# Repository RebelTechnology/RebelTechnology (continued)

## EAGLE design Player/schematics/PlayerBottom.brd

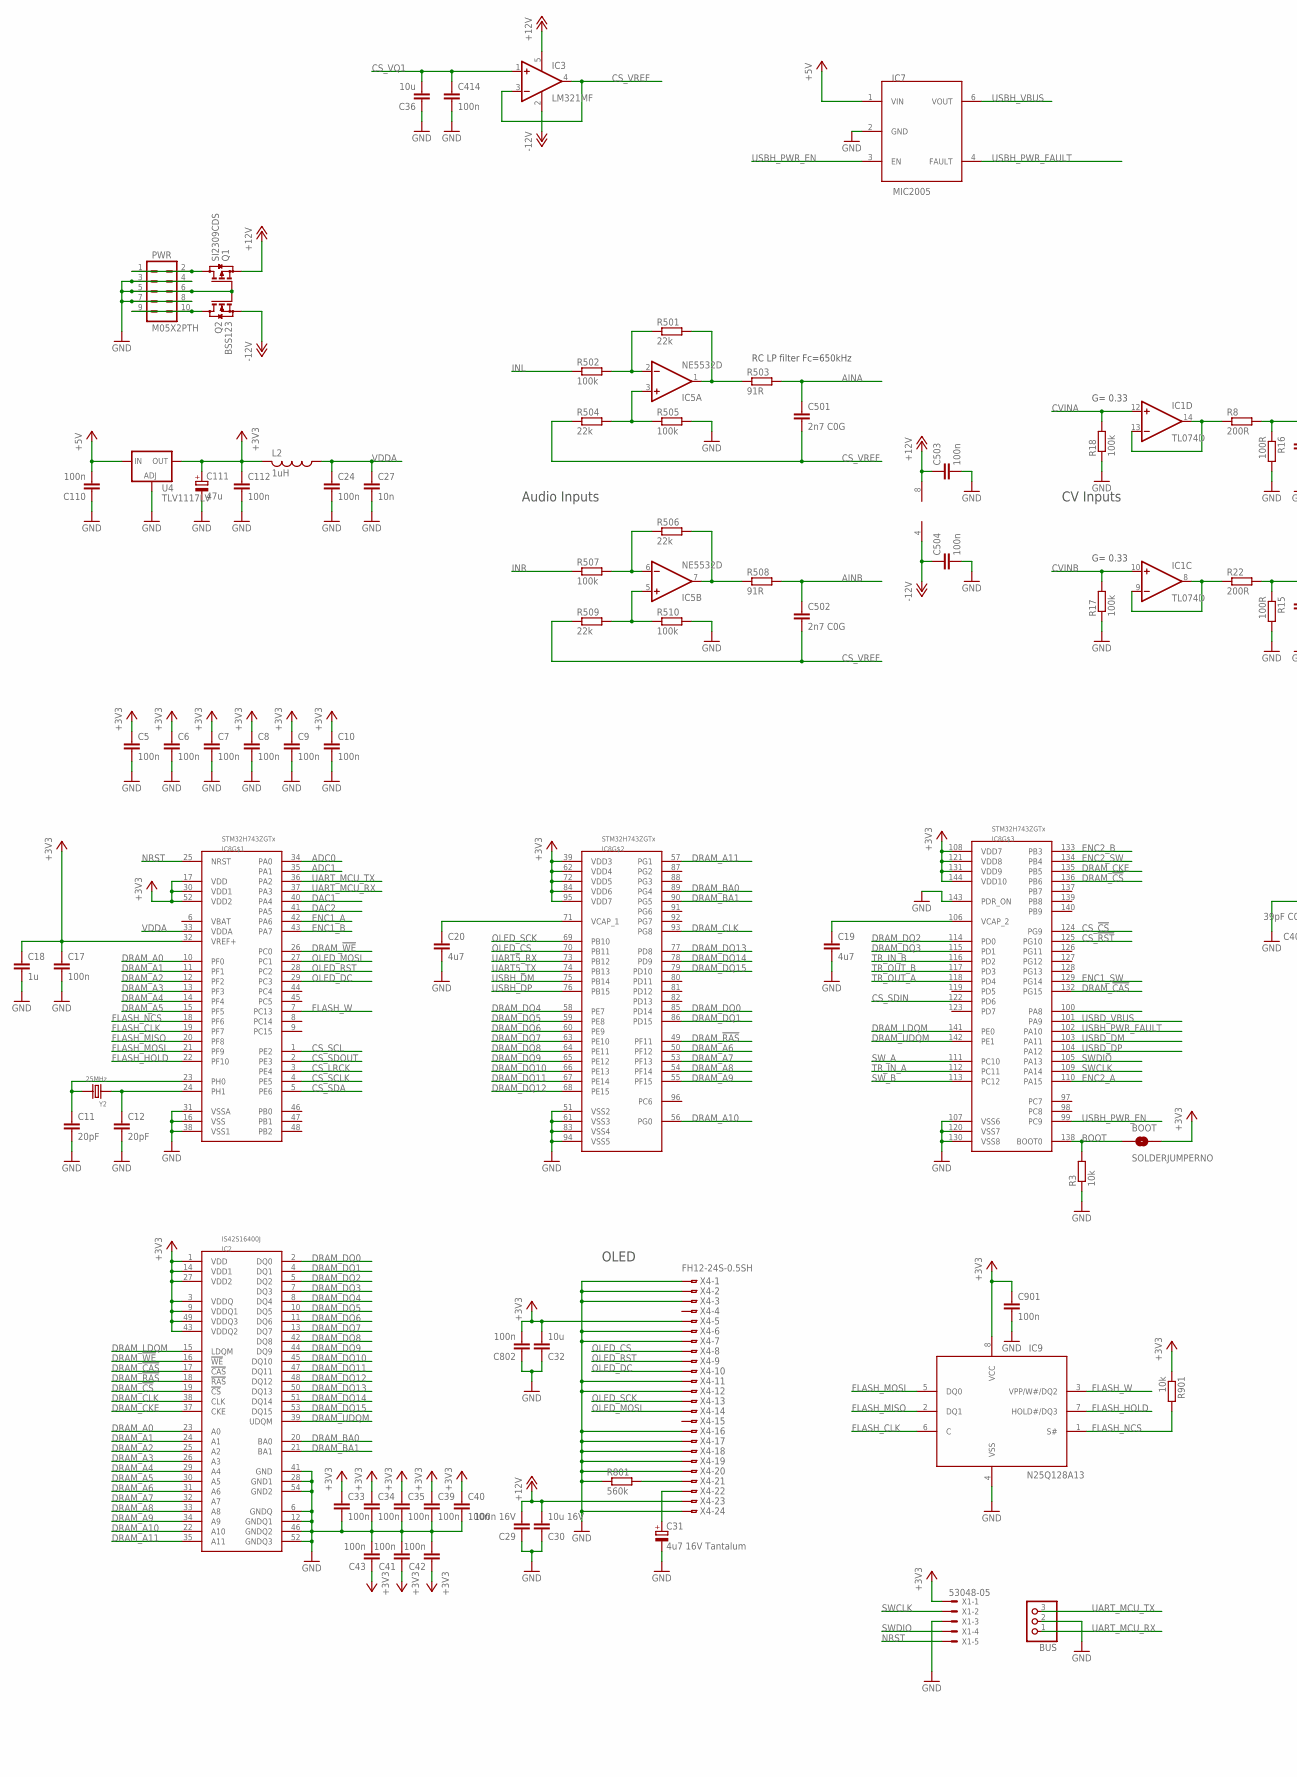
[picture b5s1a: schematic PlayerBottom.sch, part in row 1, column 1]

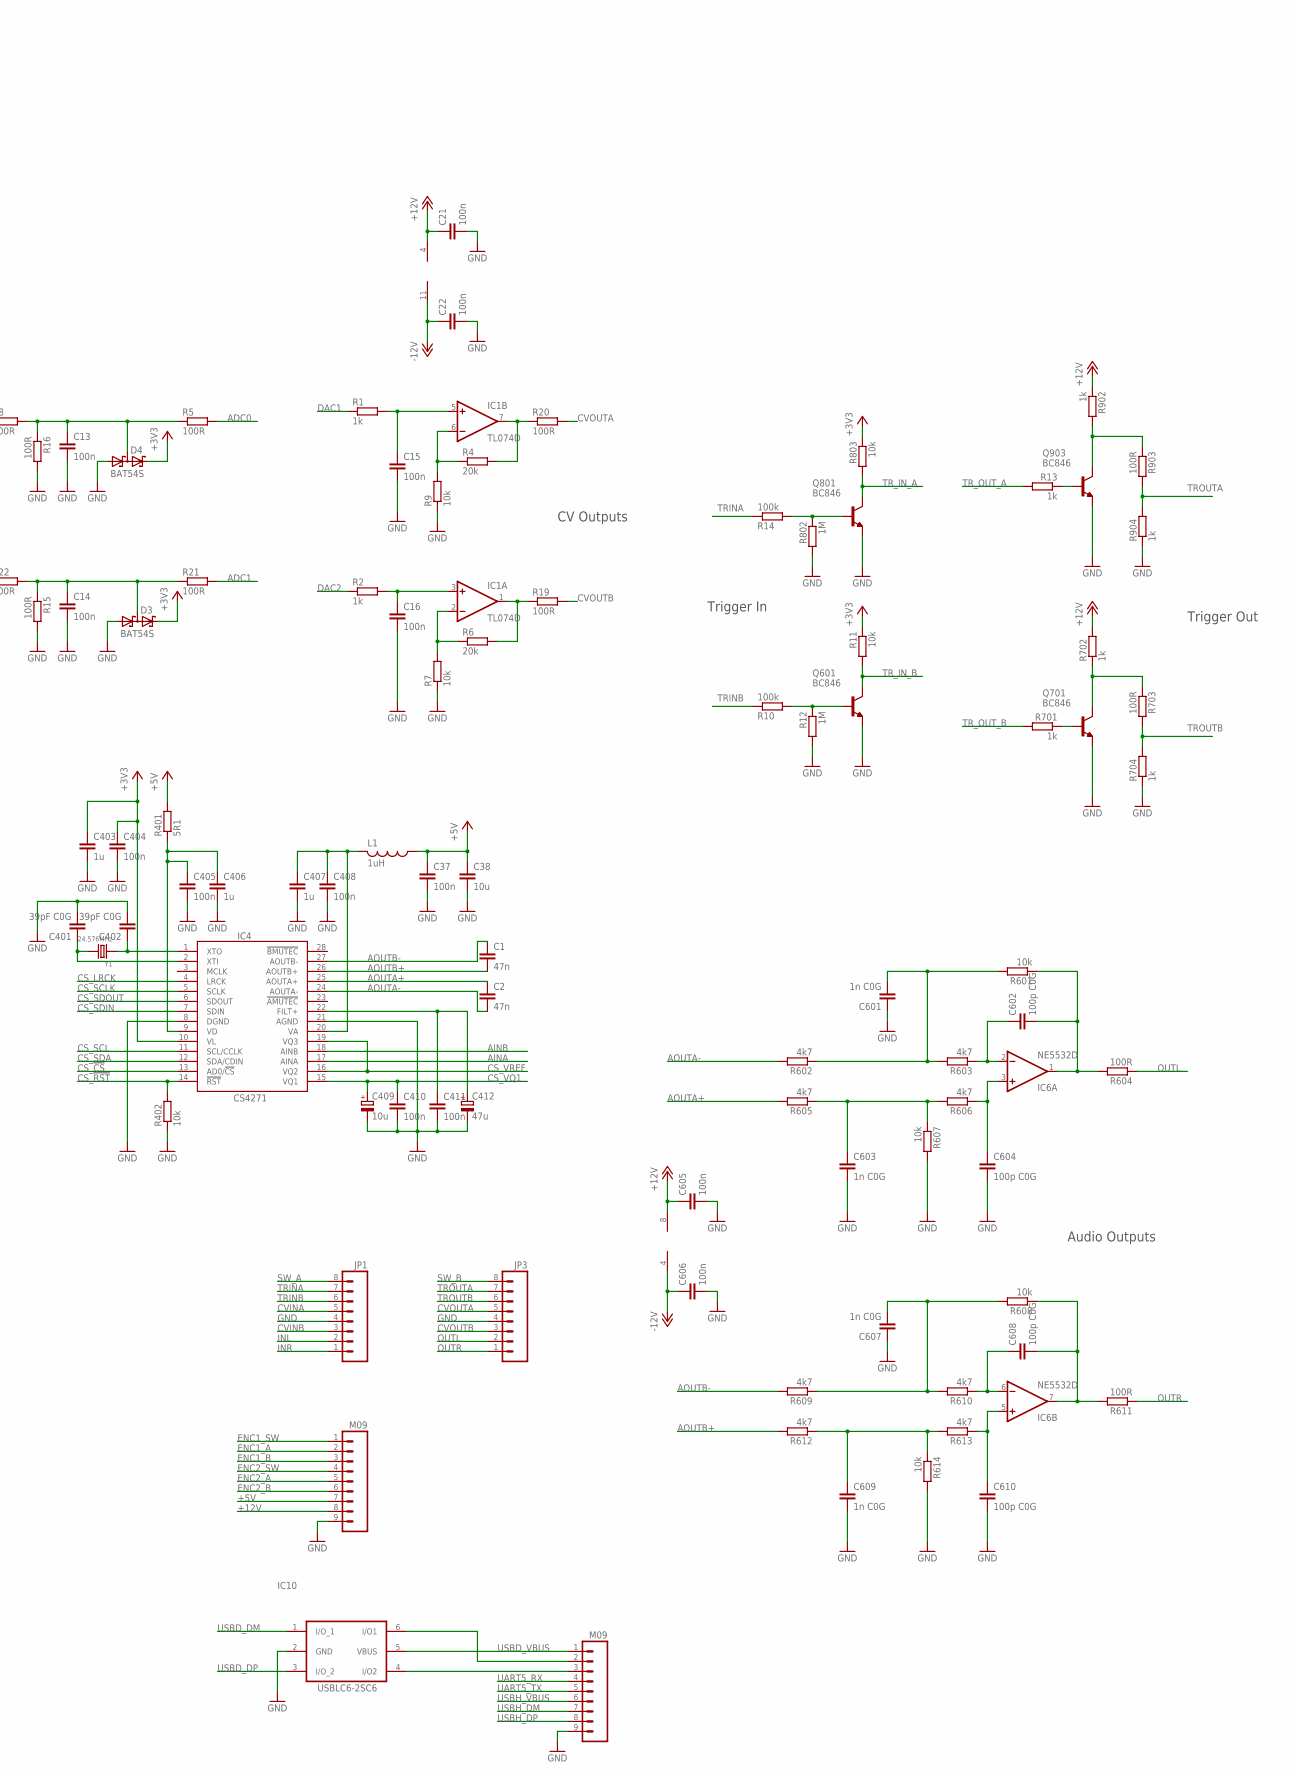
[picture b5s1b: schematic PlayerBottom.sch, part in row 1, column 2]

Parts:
BOOT: SOLDERJUMPERNO; SJ_2S-NO
BUS: CON-JST-1X03PH-TH; JST-B3B-PH-KL
C1, C2: 47n; C0603
C5, C6, C7, C8, C9, C10, C13, C14, C15, C16, C17, C21, C22, C24, C33, C34, C35, C37, C39, C40, C41, C42, C43, C110, C112, C404, C405, C408, C410, C411, C414, C503, C504, C605, C606, C802, C901: 100n; C0603
C11, C12: 20pF; C0603
C18, C403, C406, C407: 1u; C0603
C19, C20: 4u7; C0603
C27: 10n; C0603
C29: 100n 16V; C0603
C30: 10u 16V; C1206
C31: 4u7 16V Tantalum; SMC_A
C32, C36, C38: 10u; C1206
C111, C412: 47u; CPOL-5
C401, C402: 39pF C0G; C0603
C409: 10u; CPOL-5
C501, C502: 2n7 C0G; C0603
C601, C603, C607, C609: 1n C0G; C0603
C602, C604, C608, C610: 100p C0G; C0603
D3, D4: BAT54S; SOT23
IC1: TL074D; SO14
IC2: IS42S16400J; TSOP54-400
IC3: LM321MF; SOT23-5
IC4: CS4271; TSSOP28-0.65-9.7X4.4MM
IC5, IC6: NE5532D; SO08
IC7: MIC2005; SOT23-6
IC8: STM32H743ZGTx; QFP50P2200X2200X160-144N
IC9: N25Q128A13; SO8W
IC10: USBLC6-2SC6; SOT-23-6L
JP1, JP3: M081X08; 1X08
JP2, JP4: M09; 1X09
L1, L2: 1uH; 0603
PWR: M05X2PTH; AVR_ICSP
Q1: SI2309CDS; SOT23
Q2: BSS123; SOT23
Q601, Q701, Q801, Q903: BC846; SOT23
R1, R2, R13, R701, R702, R704, R902, R904: 1k; 0603
R3, R7, R9, R11, R402, R601, R607, R608, R614, R803, R901: 10k; 0603
R4, R6: 20k; 0603
R5, R15, R16, R19, R20, R21, R604, R611, R703, R903: 100R; 0603
R8, R22: 200R; 0603
R10, R14, R17, R18, R502, R505, R507, R510: 100k; 0603
R12, R802: 1M; 0603
R401: 5R1; 0603
R501, R504, R506, R509: 22k; 0603
R503, R508: 91R; 0603
R602, R603, R605, R606, R609, R610, R612, R613: 4k7; 0603
R801: 560k; 0603
U4: TLV1117LV; SOT223
X1: 53048-05
X4: FH12-24S-0.5SH
Y1: 24.576MHz; X2-SMD-5.0X3.2X1.3MM
Y2: 25MHz; X2-SMD-5.0X3.2X1.3MM

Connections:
+3.3V: BOOT.2, C5.1, C6.1, C7.1, C8.1, C9.1, C10.1, C17.1, C18.1, C32.2, C33.1, C34.1, C35.1, C39.1, C40.1, C41.1, C42.1, C43.1, C111.+, C112.1, C403.1, C404.1, C802.2, C901.1, D3.2 (C2), D4.2 (C2), IC2.1 (VDD), IC2.3 (VDDQ), IC2.9 (VDDQ1), IC2.14 (VDD1), IC2.27 (VDD2), IC2.43 (VDDQ2), IC2.49 (VDDQ3), IC4.10 (VL), IC8.17 (VDD), IC8.30 (VDD1), IC8.32 (VREF+), IC8.39 (VDD3), IC8.52 (VDD2), IC8.62 (VDD4), IC8.72 (VDD5), IC8.84 (VDD6), IC8.95 (VDD7), IC8.108 (VDD7), IC8.121 (VDD8), IC8.131 (VDD9), IC8.144 (VDD10), IC9.8 (VCC), L2.2, R11.1, R803.1, R901.1, U4.4 (OUT), X1.1, X4.5
+5V: C37.1, C38.1, C110.2, IC7.1 (VIN), JP4.7, L1.1, R401.2, U4.3 (IN)
+12V: C21.1, C29.2, C30.2, C503.1, C605.1, IC1.4 (V+), IC3.5 (V+), IC5.8 (V+), IC6.8 (V+), JP4.8, Q1.2 (S), R702.2, R902.1, X4.23
-12V: C22.1, C504.1, C606.1, IC1.11 (V-), IC3.2 (V-), IC5.4 (V-), IC6.4 (V-), Q2.2 (S)
ADC0: IC8.34 (PA0), R5.2
ADC1: IC8.35 (PA1), R21.2
AINA: C501.1, IC4.17 (AINA), R503.2
AINB: C502.1, IC4.18 (AINB), R508.2
ANALOG_OUTA: C602.2, IC6.1 (OUT), R601.1, R604.2
ANALOG_OUTB: C608.2, IC6.7 (OUT), R608.1, R611.2
AOUTA+: C2.1, IC4.25 (AOUTA+), R605.2
AOUTA-: C2.2, IC4.24 (AOUTA-), R602.2
AOUTB+: C1.2, IC4.26 (AOUTB+), R612.2
AOUTB-: C1.1, IC4.27 (AOUTB-), R609.2
BOOT: BOOT.1, IC8.138 (BOOT0), R3.2
CS_!CS: IC4.13 (AD0/!CS), IC8.124 (PG9)
CS_!RST: IC4.14 (!RST), IC8.125 (PG10), R402.2
CS_LRCK: IC4.4 (LRCK), IC8.3 (PE4)
CS_SCK: IC4.11 (SCL/CCLK), IC8.1 (PE2)
CS_SCLK: IC4.5 (SCLK), IC8.4 (PE5)
CS_SDA: IC4.12 (SDA/CDIN), IC8.5 (PE6)
CS_SDIN: IC4.7 (SDIN), IC8.122 (PD6)
CS_SDOUT: IC4.6 (SDOUT), IC8.2 (PE3)
CS_VQ1: C36.2, C409.+, C410.1, C414.1, IC3.1 (+IN), IC4.15 (VQ1)
CS_VREF: C501.2, C502.2, IC3.3 (-IN), IC3.4 (OUT), IC4.16 (VQ2), IC4.19 (VQ3), R504.1, R509.1
CVINA: IC1.12 (+IN), JP1.5, R18.2
CVINB: IC1.10 (+IN), JP1.3, R17.2
CVOUTA: JP3.5, R20.2
CVOUTB: JP3.3, R19.2
DAC1: IC8.40 (PA4), R1.1
DAC2: IC8.41 (PA5), R2.1
DRAM_!CAS: IC2.17 (!CAS), IC8.132 (PG15)
DRAM_!CS: IC2.19 (!CS), IC8.136 (PB6)
DRAM_!RAS: IC2.18 (!RAS), IC8.49 (PF11)
DRAM_!WE: IC2.16 (!WE), IC8.26 (PC0)
DRAM_A0: IC2.23 (A0), IC8.10 (PF0)
DRAM_A1: IC2.24 (A1), IC8.11 (PF1)
DRAM_A2: IC2.25 (A2), IC8.12 (PF2)
DRAM_A3: IC2.26 (A3), IC8.13 (PF3)
DRAM_A4: IC2.29 (A4), IC8.14 (PF4)
DRAM_A5: IC2.30 (A5), IC8.15 (PF5)
DRAM_A6: IC2.31 (A6), IC8.50 (PF12)
DRAM_A7: IC2.32 (A7), IC8.53 (PF13)
DRAM_A8: IC2.33 (A8), IC8.54 (PF14)
DRAM_A9: IC2.34 (A9), IC8.55 (PF15)
DRAM_A10: IC2.22 (A10), IC8.56 (PG0)
DRAM_A11: IC2.35 (A11), IC8.57 (PG1)
DRAM_BA0: IC2.20 (BA0), IC8.89 (PG4)
DRAM_BA1: IC2.21 (BA1), IC8.90 (PG5)
DRAM_CKE: IC2.37 (CKE), IC8.135 (PB5)
DRAM_CLK: IC2.38 (CLK), IC8.93 (PG8)
DRAM_DQ0: IC2.2 (DQ0), IC8.85 (PD14)
DRAM_DQ1: IC2.4 (DQ1), IC8.86 (PD15)
DRAM_DQ2: IC2.5 (DQ2), IC8.114 (PD0)
DRAM_DQ3: IC2.7 (DQ3), IC8.115 (PD1)
DRAM_DQ4: IC2.8 (DQ4), IC8.58 (PE7)
DRAM_DQ5: IC2.10 (DQ5), IC8.59 (PE8)
DRAM_DQ6: IC2.11 (DQ6), IC8.60 (PE9)
DRAM_DQ7: IC2.13 (DQ7), IC8.63 (PE10)
DRAM_DQ8: IC2.42 (DQ8), IC8.64 (PE11)
DRAM_DQ9: IC2.44 (DQ9), IC8.65 (PE12)
DRAM_DQ10: IC2.45 (DQ10), IC8.66 (PE13)
DRAM_DQ11: IC2.47 (DQ11), IC8.67 (PE14)
DRAM_DQ12: IC2.48 (DQ12), IC8.68 (PE15)
DRAM_DQ13: IC2.50 (DQ13), IC8.77 (PD8)
DRAM_DQ14: IC2.51 (DQ14), IC8.78 (PD9)
DRAM_DQ15: IC2.53 (DQ15), IC8.79 (PD10)
DRAM_LDQM: IC2.15 (LDQM), IC8.141 (PE0)
DRAM_UDQM: IC2.39 (UDQM), IC8.142 (PE1)
ENC1_A: IC8.42 (PA6), JP4.2
ENC1_B: IC8.43 (PA7), JP4.3
ENC1_SW: IC8.129 (PG14), JP4.1
ENC2_A: IC8.110 (PA15), JP4.5
ENC2_B: IC8.133 (PB3), JP4.6
ENC2_SW: IC8.134 (PB4), JP4.4
FLASH_CLK: IC8.19 (PF7), IC9.6 (C)
FLASH_HOLD: IC8.22 (PF10), IC9.7 (HOLD#/DQ3)
FLASH_MISO: IC8.20 (PF8), IC9.2 (DQ1)
FLASH_MOSI: IC8.21 (PF9), IC9.5 (DQ0)
FLASH_NCS: IC8.18 (PF6), IC9.1 (S#), R901.2
FLASH_W: IC8.7 (PC13), IC9.3 (VPP/W#/DQ2)
GND: BUS.2, C5.2, C6.2, C7.2, C8.2, C9.2, C10.2, C11.2, C12.2, C13.2, C14.2, C15.2, C16.2, C17.2, C18.2, C19.2, C20.2, C21.2, C22.2, C24.2, C27.2, C29.1, C30.1, C31.-, C31.C, C32.1, C33.2, C34.2, C35.2, C36.1, C37.2, C38.2, C39.2, C40.2, C41.2, C42.2, C43.2, C110.1, C111.-, C112.2, C401.2, C402.2, C403.2, C404.2, C405.2, C406.2, C407.2, C408.2, C409.-, C410.2, C411.2, C412.-, C414.2, C503.2, C504.2, C601.1, C603.2, C604.2, C605.2, C606.2, C607.1, C609.2, C610.2, C802.1, C901.2, D3.1 (A1), D4.1 (A1), IC2.6 (GNDQ), IC2.12 (GNDQ1), IC2.28 (GND1), IC2.41 (GND), IC2.46 (GNDQ2), IC2.52 (GNDQ3), IC2.54 (GND2), IC4.8 (DGND), IC4.21 (AGND), IC7.2 (GND), IC8.16 (VSS), IC8.31 (VSSA), IC8.38 (VSS1), IC8.51 (VSS2), IC8.61 (VSS3), IC8.83 (VSS4), IC8.94 (VSS5), IC8.107 (VSS6), IC8.120 (VSS7), IC8.130 (VSS8), IC8.143 (PDR_ON), IC9.4 (VSS), IC10.2 (GND), JP1.4, JP2.9, JP3.4, JP4.9, PWR.3, PWR.4, PWR.5, PWR.6, PWR.7, PWR.8, Q1.1 (G), Q2.1 (G), Q601.2 (E), Q701.2 (E), Q801.2 (E), Q903.2 (E), R3.1, R7.1, R9.1, R12.2, R15.2, R16.2, R17.1, R18.1, R402.1, R505.2, R510.2, R607.2, R614.2, R704.1, R801.1, R802.2, R904.1, U4.1 (ADJ), X1.3, X4.1, X4.2, X4.3, X4.6, X4.7, X4.11, X4.12, X4.16, X4.17, X4.18, X4.19, X4.20, X4.24
INL: JP1.2, R502.1
INR: JP1.1, R507.1
unnamed: C603.1, R605.1, R606.2, R607.1
unnamed: C13.1, D4.3 (C1A2), R5.1, R8.2, R16.1
unnamed: C407.1, C408.1, IC4.20 (VA), L1.2
unnamed: IC1.7 (OUT), R4.2, R20.1
unnamed: IC1.8 (OUT), IC1.9 (-IN), R22.1
unnamed: C31.+, C31.A, X4.22
unnamed: PWR.9, PWR.10, Q2.3 (D)
unnamed: R801.2, X4.21
unnamed: PWR.1, PWR.2, Q1.3 (D)
unnamed: C601.2, R601.2, R602.1, R603.2
unnamed: C12.1, IC8.24 (PH1), Y2.1
unnamed: IC1.2 (-IN), R6.1, R7.2
unnamed: C602.1, IC6.2 (-IN), R603.1
unnamed: C604.1, IC6.3 (+IN), R606.1
unnamed: IC1.6 (-IN), R4.1, R9.2
unnamed: C11.1, IC8.23 (PH0), Y2.2
unnamed: C402.1, IC4.1 (XTO), Y1.1
unnamed: IC10.6 (I/O1), JP2.2
unnamed: C411.1, C412.+, IC4.22 (FILT+)
unnamed: C401.1, IC4.2 (XTI), Y1.2
unnamed: C14.1, D3.3 (C1A2), R15.1, R21.1, R22.2
unnamed: C609.1, R612.1, R613.2, R614.1
unnamed: C607.2, R608.2, R609.1, R610.2
unnamed: C608.1, IC6.6 (-IN), R610.1
unnamed: C610.1, IC6.5 (+IN), R613.1
unnamed: IC1.13 (-IN), IC1.14 (OUT), R8.1
unnamed: C16.1, IC1.3 (+IN), R2.2
unnamed: IC1.1 (OUT), R6.2, R19.1
unnamed: C19.1, IC8.106 (VCAP_2)
unnamed: C20.1, IC8.71 (VCAP_1)
unnamed: IC5.3 (+IN), R504.2, R505.1
unnamed: Q601.1 (B), R10.2, R12.1
unnamed: IC5.2 (-IN), R501.1, R502.2
unnamed: Q701.1 (B), R701.1
unnamed: IC5.1 (OUT), R501.2, R503.1
unnamed: Q701.3 (C), R702.1, R703.1
unnamed: IC5.5 (+IN), R509.2, R510.1
unnamed: IC5.6 (-IN), R506.1, R507.2
unnamed: C15.1, IC1.5 (+IN), R1.2
unnamed: IC5.7 (OUT), R506.2, R508.1
unnamed: Q903.1 (B), R13.1
unnamed: Q903.3 (C), R902.2, R903.1
unnamed: Q801.1 (B), R14.2, R802.1
unnamed: IC10.4 (I/O2), JP2.3
NRST: IC8.25 (NRST), X1.5
OLED_CS: IC8.70 (PB11), X4.8
OLED_DC: IC8.29 (PC3), X4.10
OLED_MOSI: IC8.27 (PC1), X4.14
OLED_RST: IC8.28 (PC2), X4.9
OLED_SCK: IC8.69 (PB10), X4.13
OUTL: JP3.2, R604.1
OUTR: JP3.1, R611.1
SWCLK: IC8.109 (PA14), X1.2
SWDIO: IC8.105 (PA13), X1.4
SW_A: IC8.111 (PC10), JP1.8
SW_B: IC8.113 (PC12), JP3.8
TRINA: JP1.7, R14.1
TRINB: JP1.6, R10.1
TROUTA: JP3.7, R903.2, R904.2
TROUTB: JP3.6, R703.2, R704.2
TR_IN_A: IC8.112 (PC11), Q801.3 (C), R803.2
TR_IN_B: IC8.116 (PD2), Q601.3 (C), R11.2
TR_OUT_A: IC8.118 (PD4), R13.2
TR_OUT_B: IC8.117 (PD3), R701.2
UART5_RX: IC8.73 (PB12), JP2.4
UART5_TX: IC8.74 (PB13), JP2.5
UART_MCU_RX: BUS.1, IC8.37 (PA3)
UART_MCU_TX: BUS.3, IC8.36 (PA2)
USBD_DM: IC8.103 (PA11), IC10.1 (I/O_1)
USBD_DP: IC8.104 (PA12), IC10.3 (I/O_2)
USBD_VBUS: IC8.101 (PA9), IC10.5 (VBUS), JP2.1
USBH_DM: IC8.75 (PB14), JP2.7
USBH_DP: IC8.76 (PB15), JP2.8
USBH_PWR_EN: IC7.3 (EN), IC8.99 (PC9)
USBH_PWR_FAULT: IC7.4 (FAULT), IC8.102 (PA10)
USBH_VBUS: IC7.6 (VOUT), JP2.6
VD: C405.1, C406.1, IC4.9 (VD), R401.1
VDDA: C24.1, C27.1, IC8.33 (VDDA), L2.1

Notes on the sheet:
RC LP filter Fc=650kHz
Audio Outputs
Audio Inputs
CV Inputs
G= 0.33
CV Outputs
Trigger In
Trigger Out
OLED

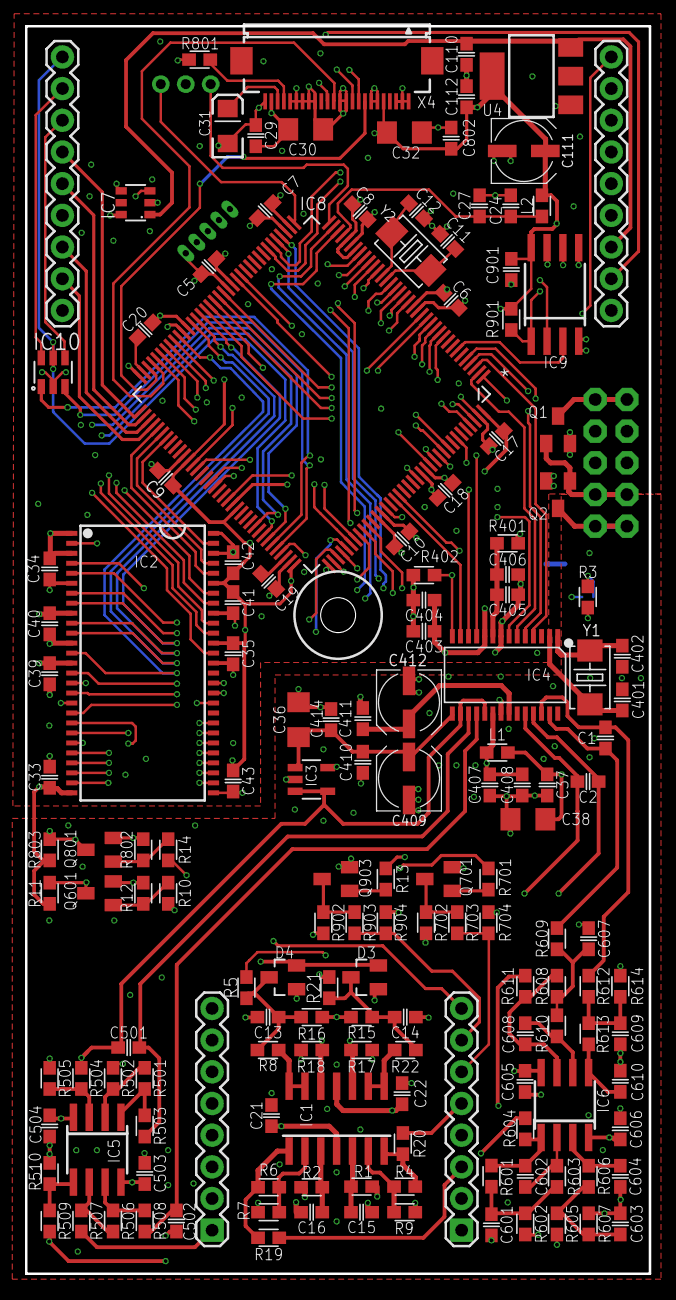
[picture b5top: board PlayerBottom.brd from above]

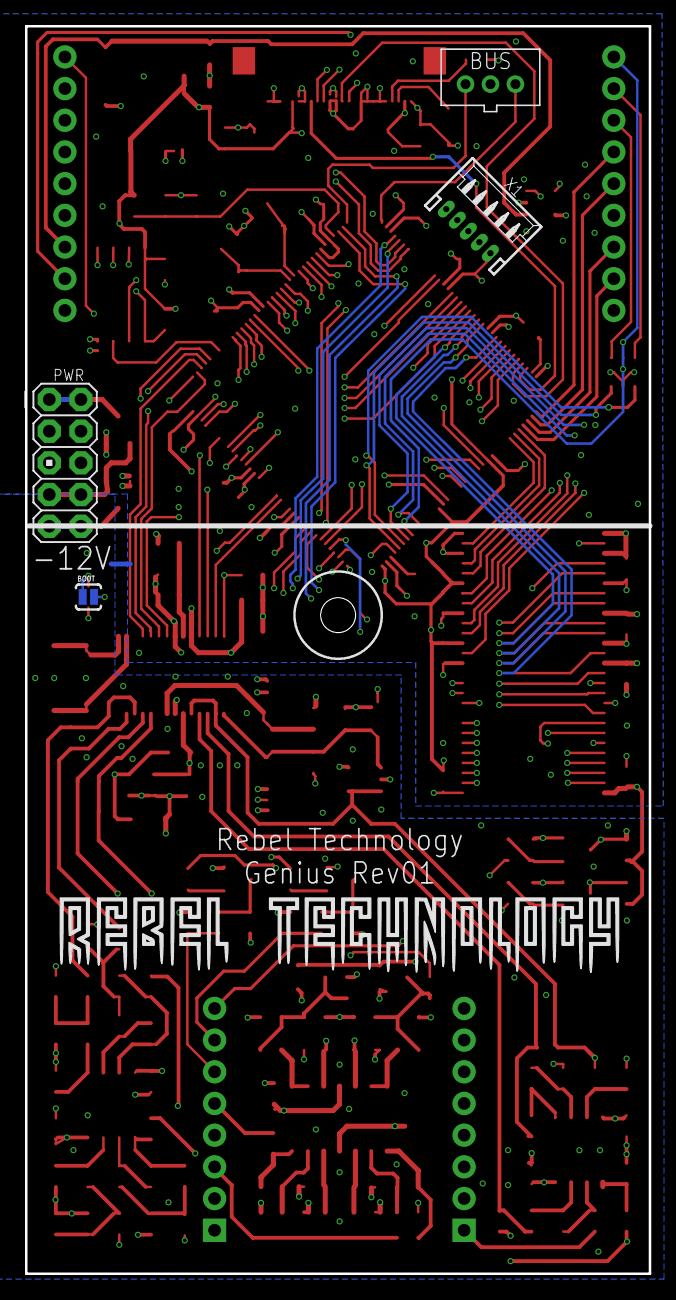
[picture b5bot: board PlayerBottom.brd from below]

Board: 4 copper layers, 50.0 x 100.0 mm, 160 parts (4 on the bottom side), 162 nets.

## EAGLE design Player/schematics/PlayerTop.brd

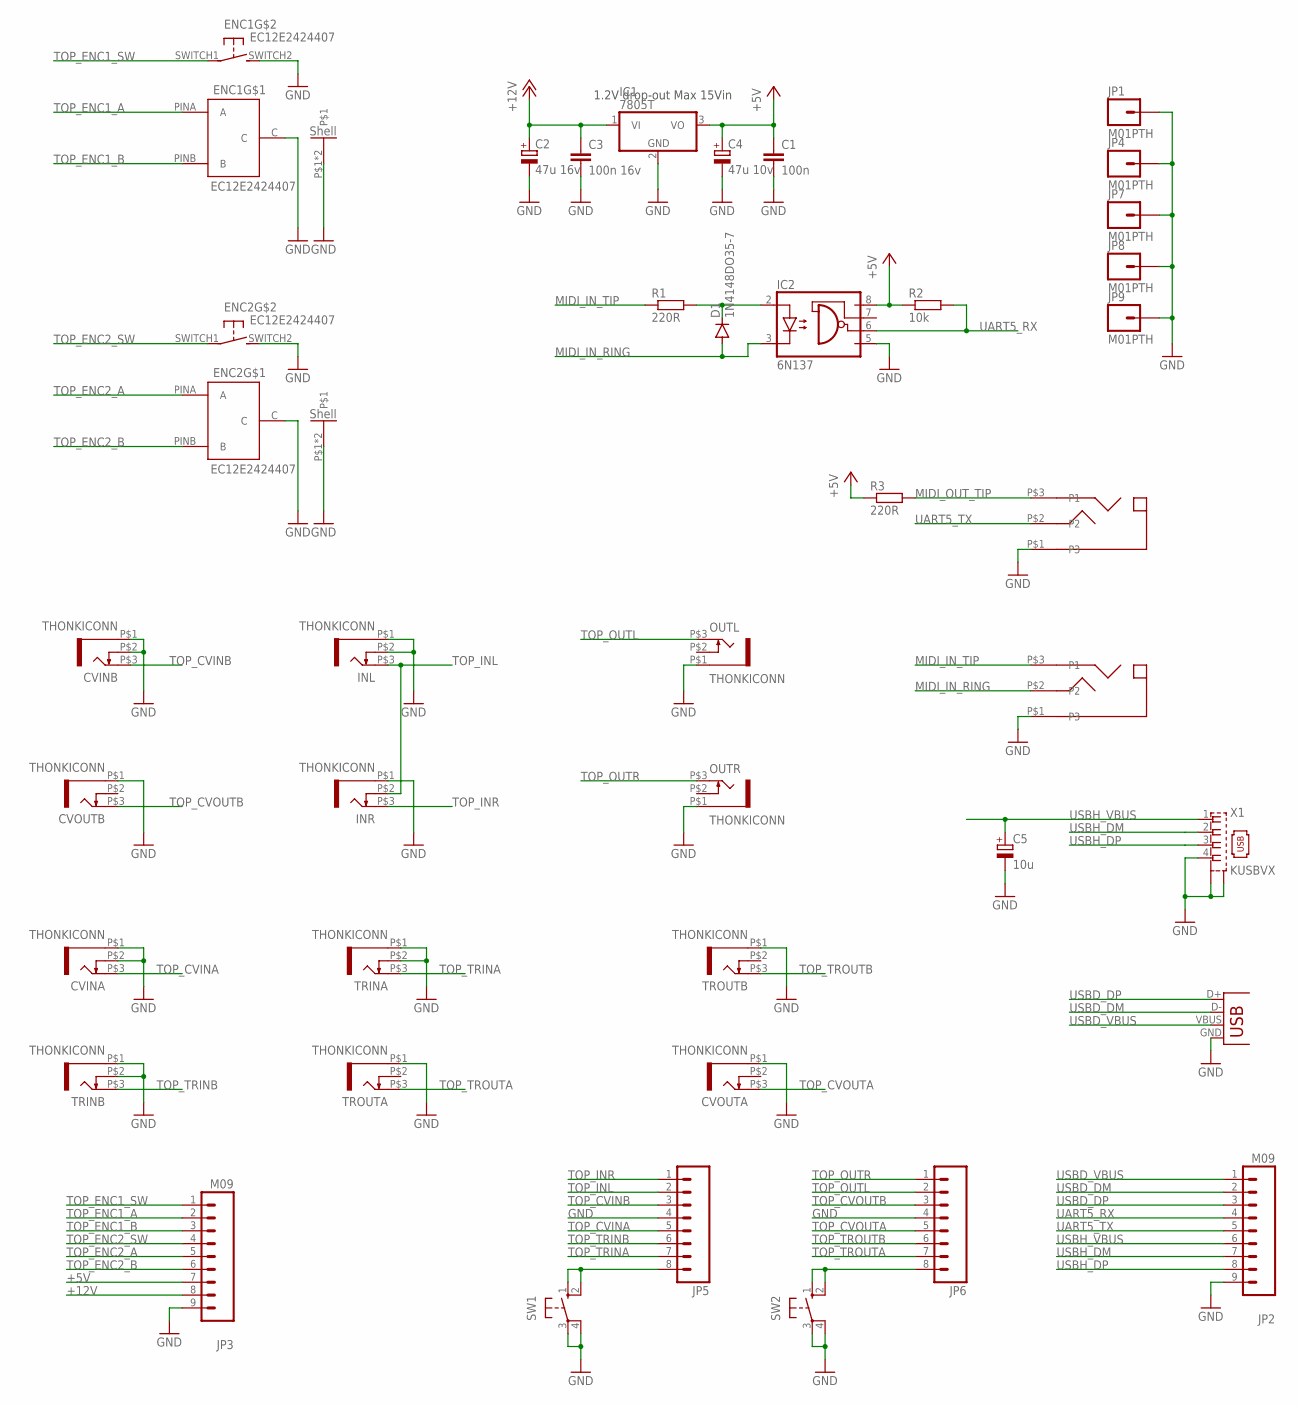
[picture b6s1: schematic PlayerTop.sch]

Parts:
C1: 100n; C050-024X044
C2: 47u 16v; E5-6
C3: 100n 16v; C050-024X044
C4: 47u 10v; E5-6
C5: 10u; E2,5-6
CVINA: THONKICONN
CVINB: THONKICONN
CVOUTA: THONKICONN
CVOUTB: THONKICONN
D1: 1N4148DO35-7; DO35-7
ENC1, ENC2: EC12E2424407
IC1: 7805T; TO220H
IC2: 6N137; DIL08
INL: THONKICONN
INR: THONKICONN
JP1, JP4, JP7, JP8, JP9: M01PTH; 1X01
JP2, JP3: M09; 1X09
JP5, JP6: M081X08; 1X08
MIDI_IN: THONKICONN_STEREO
MIDI_OUT: THONKICONN_STEREO
OUTL: THONKICONN
OUTR: THONKICONN
R1, R3: 220R; 0204/7
R2: 10k; 0204/7
SW1, SW2: 10-XX; B3F-10XX
TRINA: THONKICONN
TRINB: THONKICONN
TROUTA: THONKICONN
TROUTB: THONKICONN
X1: KUSBVX
X2: USBPTH-VERTICAL; USB-B-PTH-VERTICAL

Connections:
+5V: C1.1, C4.+, IC1.3 (VO), IC2.8 (VCC), JP3.7, R2.1, R3.1
+12V: C2.+, C3.1, IC1.1 (VI), JP3.8
GND: C1.2, C2.-, C3.2, C4.-, C5.-, CVINA.P$1 (5), CVINA.P$2 (4), CVINB.P$1 (5), CVINB.P$2 (4), CVOUTA.P$1 (5), CVOUTB.P$1 (5), ENC1.C, ENC1.P$1, ENC1.P$2, ENC1.SWITCH2 (S), ENC2.C, ENC2.P$1, ENC2.P$2, ENC2.SWITCH2 (S), IC1.2 (GND), IC2.5 (GND), INL.P$1 (5), INL.P$2 (4), INR.P$1 (5), JP1.1, JP2.9, JP3.9, JP4.1, JP5.4, JP6.4, JP7.1, JP8.1, JP9.1, MIDI_IN.P$1 (P3), MIDI_OUT.P$1 (P3), OUTL.P$1 (5), OUTR.P$1 (5), SW1.3, SW1.4 (P1), SW2.3, SW2.4 (P1), TRINA.P$1 (5), TRINA.P$2 (4), TRINB.P$1 (5), TRINB.P$2 (4), TROUTA.P$1 (5), TROUTB.P$1 (5), X1.4, X1.M1 (S1), X1.M2 (S2), X2.GND
MIDI_IN_RING: D1.A, IC2.3 (C), MIDI_IN.P$2 (P2)
MIDI_IN_TIP: MIDI_IN.P$3 (P1), R1.1
MIDI_OUT_TIP: MIDI_OUT.P$3 (P1), R3.2
unnamed: D1.C, IC2.2 (A), R1.2
unnamed: JP5.8, SW1.1 (S), SW1.2 (S1)
unnamed: JP6.8, SW2.1 (S), SW2.2 (S1)
TOP_CVINA: CVINA.P$3 (3), JP5.5
TOP_CVINB: CVINB.P$3 (3), JP5.3
TOP_CVOUTA: CVOUTA.P$3 (3), JP6.5
TOP_CVOUTB: CVOUTB.P$3 (3), JP6.3
TOP_ENC1_A: ENC1.PINA (A), JP3.2
TOP_ENC1_B: ENC1.PINB (B), JP3.3
TOP_ENC1_SW: ENC1.SWITCH1, JP3.1
TOP_ENC2_A: ENC2.PINA (A), JP3.5
TOP_ENC2_B: ENC2.PINB (B), JP3.6
TOP_ENC2_SW: ENC2.SWITCH1, JP3.4
TOP_INL: INL.P$3 (3), INR.P$2 (4), JP5.2
TOP_INR: INR.P$3 (3), JP5.1
TOP_OUTL: JP6.2, OUTL.P$3 (3)
TOP_OUTR: JP6.1, OUTR.P$3 (3)
TOP_TRINA: JP5.7, TRINA.P$3 (3)
TOP_TRINB: JP5.6, TRINB.P$3 (3)
TOP_TROUTA: JP6.7, TROUTA.P$3 (3)
TOP_TROUTB: JP6.6, TROUTB.P$3 (3)
UART5_RX: IC2.6 (VO), JP2.4, R2.2
UART5_TX: JP2.5, MIDI_OUT.P$2 (P2)
USBD_DM: JP2.2, X2.D-
USBD_DP: JP2.3, X2.D+
USBD_VBUS: JP2.1, X2.VBUS
USBH_DM: JP2.7, X1.2
USBH_DP: JP2.8, X1.3
USBH_VBUS: C5.+, JP2.6, X1.1

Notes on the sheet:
1.2V drop-out Max 15Vin

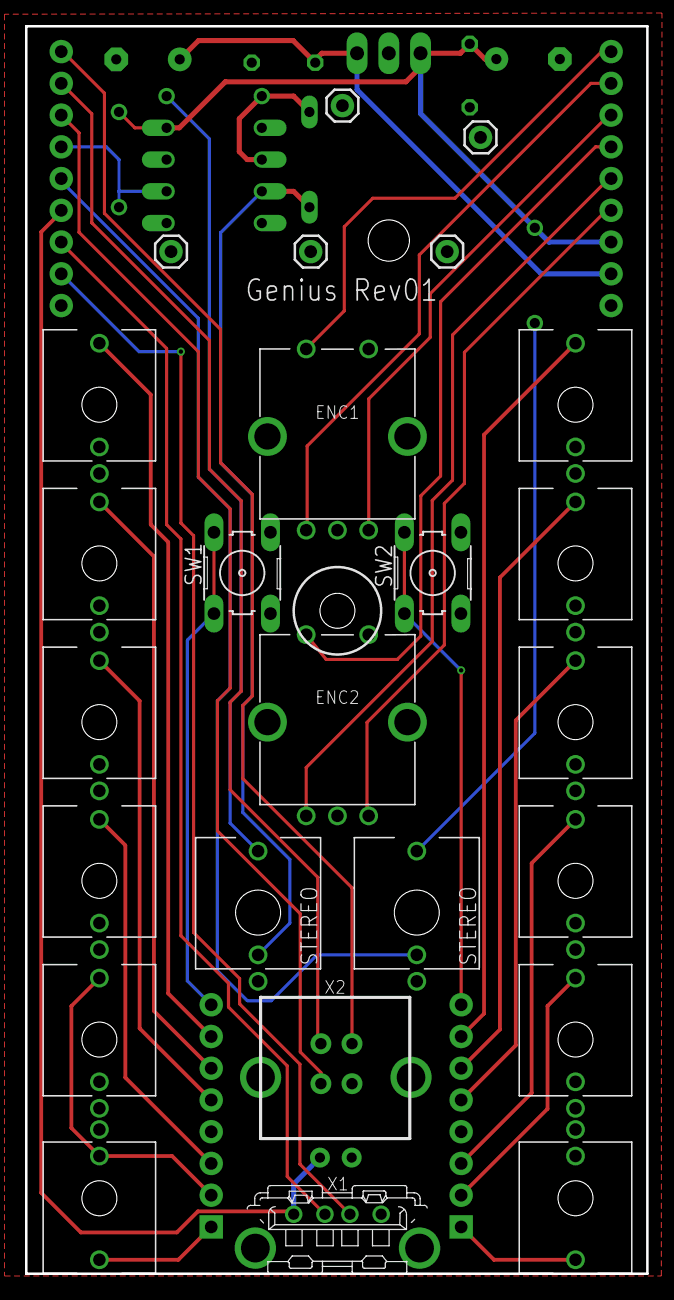
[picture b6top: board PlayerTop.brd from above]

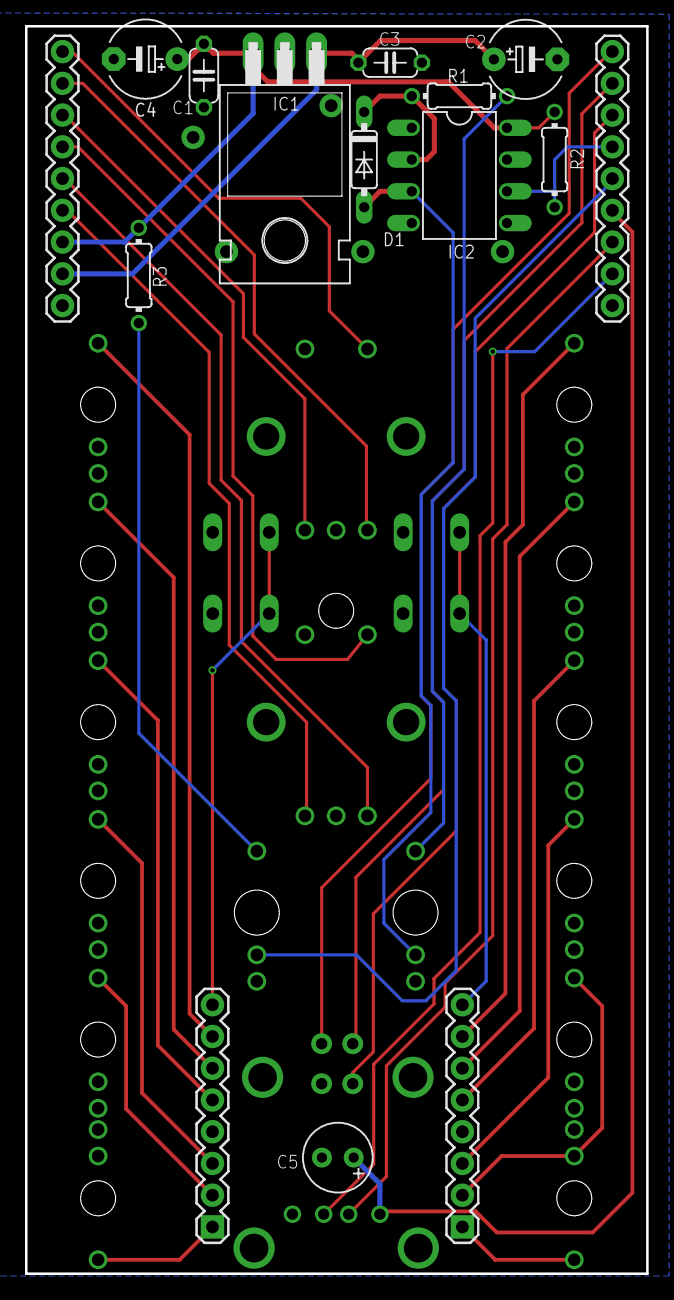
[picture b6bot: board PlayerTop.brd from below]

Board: 2 copper layers, 49.7 x 99.8 mm, 40 parts (15 on the bottom side), 35 nets.

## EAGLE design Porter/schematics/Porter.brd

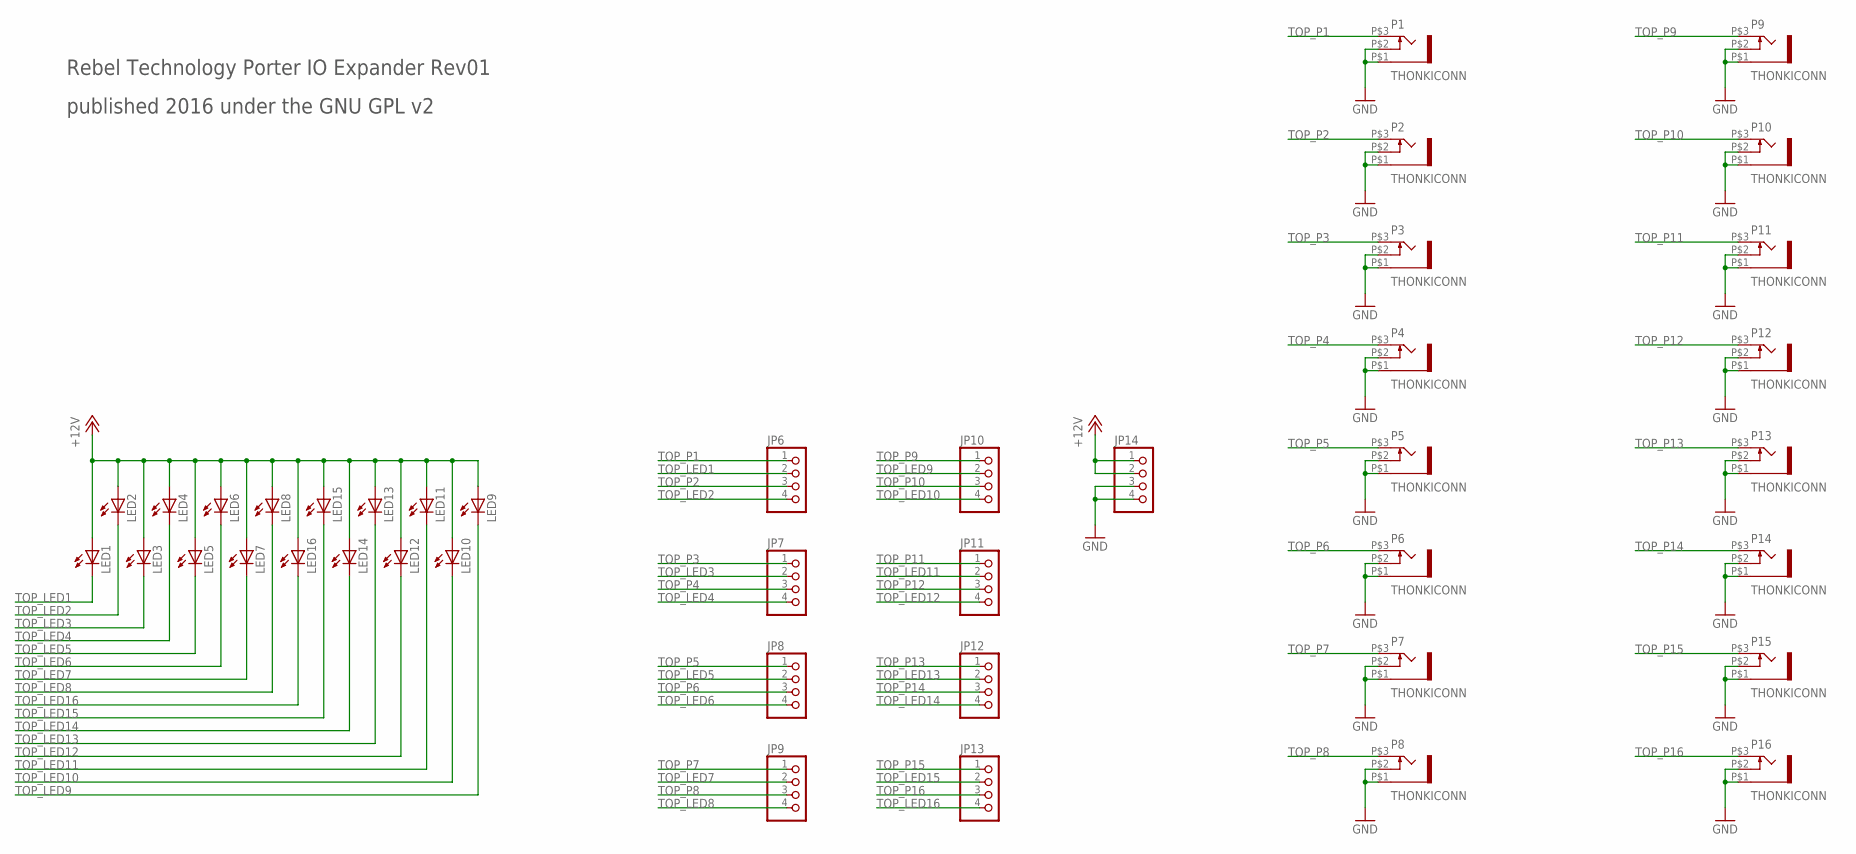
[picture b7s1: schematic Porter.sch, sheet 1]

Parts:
JP6, JP7, JP8, JP9, JP10, JP11, JP12, JP13, JP14: PINHD-1X4; 1X04
LED1, LED2, LED3, LED4, LED5, LED6, LED7, LED8, LED9, LED10, LED11, LED12, LED13, LED14, LED15, LED16: LED3MM
P1, P2, P3, P4, P5, P6, P7, P8, P9, P10, P11, P12, P13, P14, P15, P16: THONKICONN

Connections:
TOP_+12V: JP14.1, JP14.2, LED1.A, LED2.A, LED3.A, LED4.A, LED5.A, LED6.A, LED7.A, LED8.A, LED9.A, LED10.A, LED11.A, LED12.A, LED13.A, LED14.A, LED15.A, LED16.A
TOP_GND: JP14.3, JP14.4, P1.P$1 (5), P1.P$2 (4), P2.P$1 (5), P2.P$2 (4), P3.P$1 (5), P3.P$2 (4), P4.P$1 (5), P4.P$2 (4), P5.P$1 (5), P5.P$2 (4), P6.P$1 (5), P6.P$2 (4), P7.P$1 (5), P7.P$2 (4), P8.P$1 (5), P8.P$2 (4), P9.P$1 (5), P9.P$2 (4), P10.P$1 (5), P10.P$2 (4), P11.P$1 (5), P11.P$2 (4), P12.P$1 (5), P12.P$2 (4), P13.P$1 (5), P13.P$2 (4), P14.P$1 (5), P14.P$2 (4), P15.P$1 (5), P15.P$2 (4), P16.P$1 (5), P16.P$2 (4)
TOP_LED1: JP6.2, LED1.K (C)
TOP_LED2: JP6.4, LED2.K (C)
TOP_LED3: JP7.2, LED3.K (C)
TOP_LED4: JP7.4, LED4.K (C)
TOP_LED5: JP8.2, LED5.K (C)
TOP_LED6: JP8.4, LED6.K (C)
TOP_LED7: JP9.2, LED7.K (C)
TOP_LED8: JP9.4, LED8.K (C)
TOP_LED9: JP10.2, LED9.K (C)
TOP_LED10: JP10.4, LED10.K (C)
TOP_LED11: JP11.2, LED11.K (C)
TOP_LED12: JP11.4, LED12.K (C)
TOP_LED13: JP12.2, LED13.K (C)
TOP_LED14: JP12.4, LED14.K (C)
TOP_LED15: JP13.2, LED15.K (C)
TOP_LED16: JP13.4, LED16.K (C)
TOP_P1: JP6.1, P1.P$3 (3)
TOP_P2: JP6.3, P2.P$3 (3)
TOP_P3: JP7.1, P3.P$3 (3)
TOP_P4: JP7.3, P4.P$3 (3)
TOP_P5: JP8.1, P5.P$3 (3)
TOP_P6: JP8.3, P6.P$3 (3)
TOP_P7: JP9.1, P7.P$3 (3)
TOP_P8: JP9.3, P8.P$3 (3)
TOP_P9: JP10.1, P9.P$3 (3)
TOP_P10: JP10.3, P10.P$3 (3)
TOP_P11: JP11.1, P11.P$3 (3)
TOP_P12: JP11.3, P12.P$3 (3)
TOP_P13: JP12.1, P13.P$3 (3)
TOP_P14: JP12.3, P14.P$3 (3)
TOP_P15: JP13.1, P15.P$3 (3)
TOP_P16: JP13.3, P16.P$3 (3)

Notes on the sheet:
Rebel Technology Porter IO Expander Rev01
published 2016 under the GNU GPL v2
